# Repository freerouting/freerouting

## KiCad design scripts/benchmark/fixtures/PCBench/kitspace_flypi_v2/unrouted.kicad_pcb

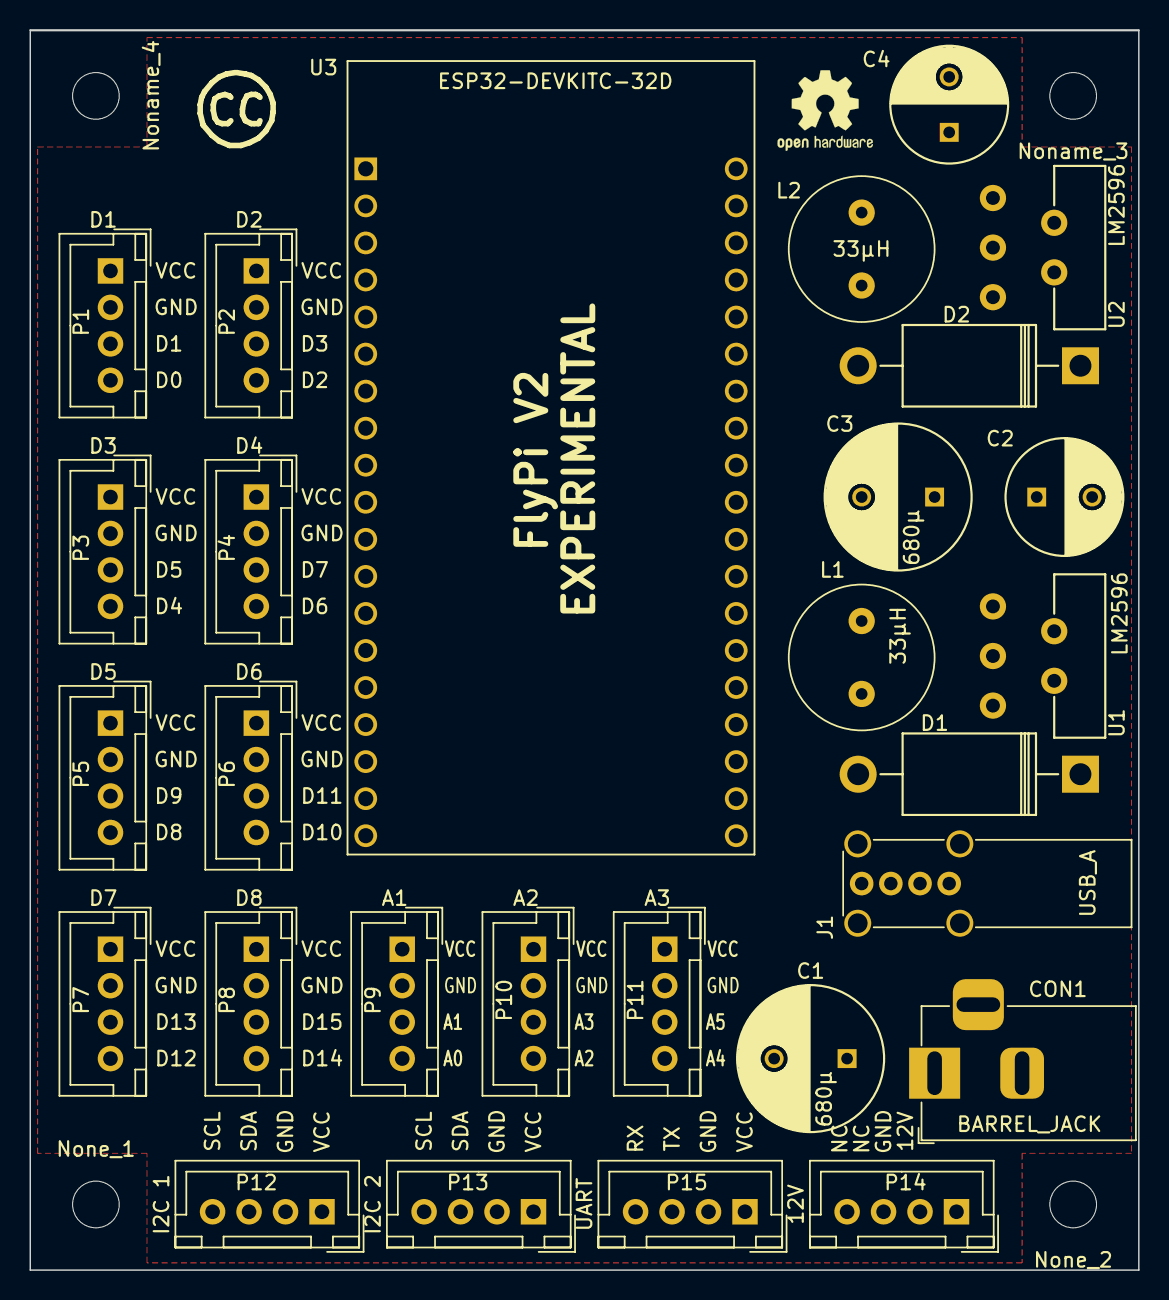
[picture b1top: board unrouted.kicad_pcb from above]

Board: 2 copper layers, 76.0 x 85.0 mm, 35 parts (0 on the bottom side), 34 nets, no tracks yet.

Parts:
C1, C3: 680µ; C_Radial_D10_L21_P5
C2, C4: 220µ; C_Radial_D8_L13_P3.8
CON1: BARREL_JACK; BarrelJack_Horizontal
D1, D2: Schottky 5A; Diode_DO-201AD_Horizontal_RM15
J1: USB_A; USB_A_Vertical
L1, L2: 33µH; Neosid_Inductor_MA-Bs75
Noname_1: Symbol_CreativeCommons_SilkScreenTop_Type2_Small
Noname_2: OSHW-Logo2_7.3x6mm_SilkScreen
Noname_3, Noname_4: MountingHole_3.2mm_M3_DIN965
Noname_5: (no value)
None_1, None_2: MountingHole_3.2mm_M3_DIN965
P1: D1; JST_XH_B04B-XH-A_04x2.50mm_Straight
P2: D2; JST_XH_B04B-XH-A_04x2.50mm_Straight
P3: D3; JST_XH_B04B-XH-A_04x2.50mm_Straight
P4: D4; JST_XH_B04B-XH-A_04x2.50mm_Straight
P5: D5; JST_XH_B04B-XH-A_04x2.50mm_Straight
P6: D6; JST_XH_B04B-XH-A_04x2.50mm_Straight
P7: D7; JST_XH_B04B-XH-A_04x2.50mm_Straight
P8: D8; JST_XH_B04B-XH-A_04x2.50mm_Straight
P9: A1; JST_XH_B04B-XH-A_04x2.50mm_Straight
P10: A2; JST_XH_B04B-XH-A_04x2.50mm_Straight
P11: A3; JST_XH_B04B-XH-A_04x2.50mm_Straight
P12: I2C 1; JST_XH_B04B-XH-A_04x2.50mm_Straight
P13: I2C 2; JST_XH_B04B-XH-A_04x2.50mm_Straight
P14: 12V; JST_XH_B04B-XH-A_04x2.50mm_Straight
P15: UART; JST_XH_B04B-XH-A_04x2.50mm_Straight
U1, U2: LM2596
U3: ESP32-DEVKITC-32D; MODULE_ESP32-DEVKITC-32D

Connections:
+5V: C4.1, L2.2, P1.1, P2.1, P3.1, P4.1, P5.1, P6.1, P7.1, P8.1, P9.1, P10.1, P11.1, P12.1, P13.1, P15.1, U2.4, U3.19
A1-3: P9.3, U3.6
A1-4: P9.4, U3.5
A2-3: P10.3, U3.4
A2-4: P10.4, U3.3
A3-3: P11.3, U3.33
A3-4: P11.4, U3.32
D1-3: P1.3, U3.8
D1-4: P1.4, U3.7
D2-3: P2.3, U3.10
D2-4: P2.4, U3.9
D3-3: P3.3, U3.12
D3-4: P3.4, U3.11
D4-3: P4.3, U3.15
D4-4: P4.4, U3.13
D5-3: P5.3, U3.17
D5-4: P5.4, U3.16
D6-3: P6.3, U3.18
D6-4: P6.4, U3.27
D7-3: P7.3, U3.36
D7-4: P7.4, U3.37
D8-3: P8.3, U3.35
D8-4: P8.4, U3.34
GND: C1.2, C2.2, C3.2, C4.2, CON1.2, CON1.3, D1.2, D2.2, J1.4, J1.5, P1.2, P2.2, P3.2, P4.2, P5.2, P6.2, P7.2, P8.2, P9.2, P10.2, P11.2, P12.2, P13.2, P14.2, P15.2, U1.3, U1.5, U2.3, U2.5, U3.14, U3.20, U3.26
I2C_1-3: P12.3, U3.29
I2C_1-4: P12.4, U3.28
I2C_2-3: P13.3, U3.31
I2C_2-4: P13.4, U3.30
unnamed: C1.1, C3.1, CON1.1, P14.1, U1.1, U2.1
unnamed: C2.1, J1.1, L1.2, U1.4
unnamed: D1.1, L1.1, U1.2
unnamed: D2.1, L2.1, U2.2
RX: P15.4, U3.24
TX: P15.3, U3.23

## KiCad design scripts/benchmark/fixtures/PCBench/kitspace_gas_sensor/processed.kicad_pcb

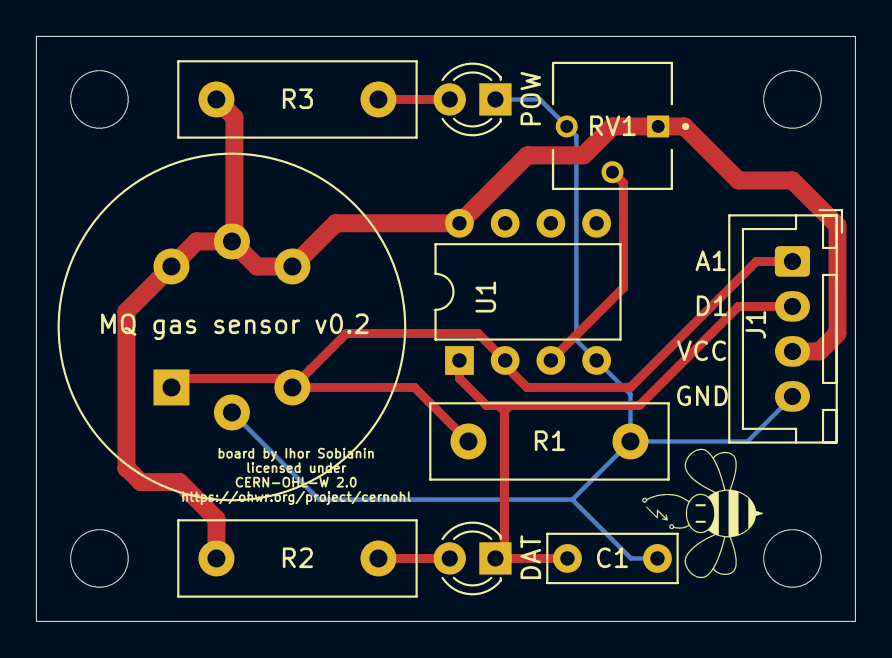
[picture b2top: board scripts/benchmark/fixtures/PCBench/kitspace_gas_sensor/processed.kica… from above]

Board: 2 copper layers, 45.5 x 32.5 mm, 10 parts (0 on the bottom side), 7 nets.

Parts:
A1: MQ-135; MQ-6
C1: 100nF; C_Disc_D7.0mm_W2.5mm_P5.00mm
D1, D2: LED; LED_D3.0mm
J1: Conn_01x04; JST_XH_B4B-XH-A_1x04_P2.50mm_Vertical
R1: 4,7k; R_Box_L13.0mm_W4.0mm_P9.00mm
R2, R3: 1k; R_Box_L13.0mm_W4.0mm_P9.00mm
RV1: R_POT; TRIM_3362P-1-103
U1: LM393; DIP-8_W7.62mm

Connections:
+5V: A1.4, A1.5, A1.6, J1.3, R2.1, R3.1, RV1.1, U1.8
A1: A1.1, A1.3, J1.1, R1.1, U1.2
D1: C1.1, D1.1, J1.2, U1.1
GND: A1.2, C1.2, D2.1, J1.4, R1.2, RV1.3, U1.4
unnamed: D1.2, R2.2
unnamed: D2.2, R3.2
unnamed: RV1.2, U1.3

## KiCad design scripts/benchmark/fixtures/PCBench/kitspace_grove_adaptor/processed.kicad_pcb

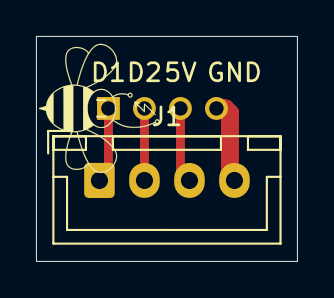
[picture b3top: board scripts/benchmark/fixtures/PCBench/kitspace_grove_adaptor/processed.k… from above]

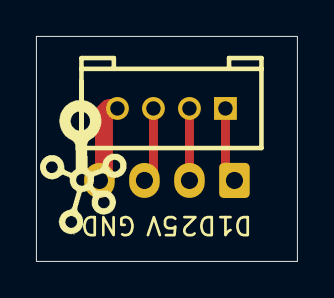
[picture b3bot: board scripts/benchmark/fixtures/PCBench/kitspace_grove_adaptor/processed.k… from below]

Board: 2 copper layers, 14.5 x 12.5 mm, 3 parts (2 on the bottom side), 4 nets.

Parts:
J1: Conn_01x04; JST_XH_B4B-XH-A_1x04_P2.50mm_Vertical
J2: Conn_01x04; 4P-LEADED-2.0
U$3: TWIGLOGO

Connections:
+5V: J1.3, J2.3
GND: J1.4, J2.4
unnamed: J1.1, J2.1
unnamed: J1.2, J2.2

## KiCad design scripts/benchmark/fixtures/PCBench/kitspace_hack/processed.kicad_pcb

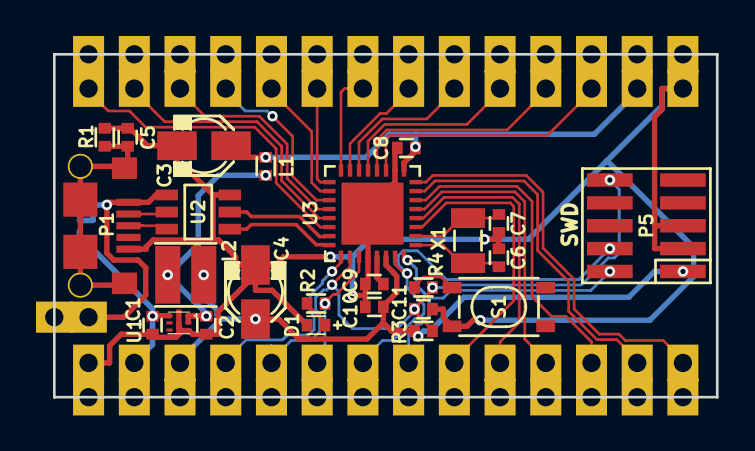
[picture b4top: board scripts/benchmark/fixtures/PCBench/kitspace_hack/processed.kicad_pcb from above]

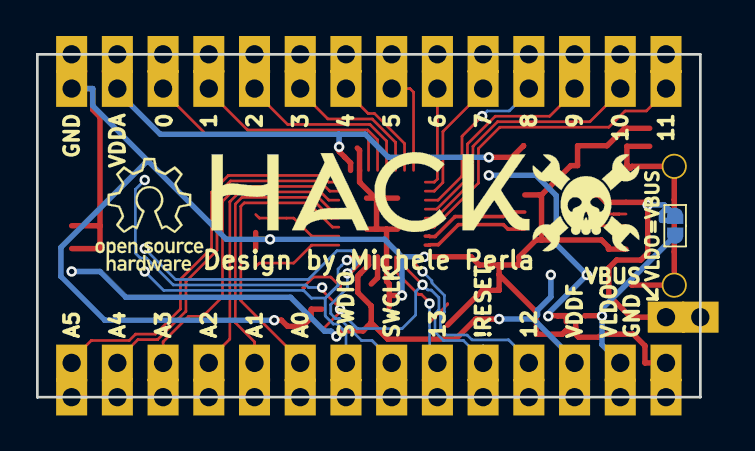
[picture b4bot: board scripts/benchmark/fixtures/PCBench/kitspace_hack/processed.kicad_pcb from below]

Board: 2 copper layers, 36.8 x 19.1 mm, 32 parts (6 on the bottom side), 39 nets.

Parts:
C1, C2: 2.2uF; C_0603
C3, C4: 10uF; c_elec_3x5.3
C5: 4.7nF; C_0603
C6, C7: 10pF; C_0603
C8, C9, C10, C11: 100nF; C_0603
D1: RED; LED_0603
JP1: Jumper_NO_Small; SMD_Jumper
L1: BLM18EG221; L_0603
L2: 10uH; ELLVFG
LOGO1: OSHW; OSHW-LOGO
LOGO2: HACKADAY; HACKADAY-LOGO
LOGO3: HACK; HACK-small
P1: USB_micro; 10118193-0001LF
P2, P3: CONN_01X14; Pin_Castellated_1x14
P4: CONN_01X01; Pin_Castellated_1x01
P5: CONN_SWD; Cortex_Debug_Connector_50mils
R1: 1M; R_0603
R2, R4: 330; R_0603
R3: 10k; R_0603
S1: RST; SPST-PTS_810
U1: MIC5528; DFN-6-1EP_1.2x1.2mm_Pitch0.4mm
U2: STF202; TSOP-6
U3: ATSAMD21E; QFN-32-1EP_5x5mm_Pitch0.5mm
X1: ABS07; xtal_3.2x1.5mm

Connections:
!RESET: C11.1, P2.5, P5.10, R3.1, R4.1, U3.26
/VDDCORE: C9.1, U3.29
/shield: C5.2, P1.6, R1.2
GND: C1.2, C2.2, C3.2, C4.2, C5.1, C6.2, C7.2, C8.2, C9.2, C10.2, C11.2, D1.2, P1.5, P2.1, P3.14, P5.3, P5.5, R1.1, S1.1, U1.3, U1.7, U2.6, U3.10, U3.28, U3.33
unnamed: D1.1, R2.2
unnamed: P1.2, U2.2
unnamed: P1.3, U2.3
unnamed: R4.2, S1.3
PA02/A0: P2.9, U3.3
PA03/A1: P2.10, U3.4
PA04/A2: P2.11, U3.5
PA05/A3: P2.12, U3.6
PA06/A4: P2.13, U3.7
PA07/A5: P2.14, U3.8
PA08/0: P3.12, U3.11
PA09/1: P3.11, U3.12
PA10/2: P3.10, U3.13
PA11/3: P3.9, U3.14
PA14/4: P3.8, U3.15
PA15/5: P3.7, U3.16
PA16/6: P3.6, U3.17
PA17/7: P3.5, U3.18
PA18/8: P3.4, U3.19
PA19/9: P3.3, U3.20
PA22/10: P3.2, U3.21
PA23/11: P3.1, U3.22
PA27/12: P2.4, U3.25
PA28/13: P2.6, R2.1, U3.27
PA30/SWCLK: P2.7, P5.4, U3.31
PA31/SWDIO: P2.8, P5.2, U3.32
USB-D+: U2.4, U3.24
USB-D-: U2.5, U3.23
VBUS: JP1.1, P1.1, P4.1, U2.1
VDD: C2.1, L1.1, L2.1, U1.1, U1.2
VDDANA: C3.1, C8.1, L1.2, P3.13, U3.9
VDDF: C4.1, C10.1, L2.2, P2.3, P5.1, R3.2, U3.30
VLDO: C1.1, JP1.2, P2.2, U1.6
XIN32: C6.1, U3.1, X1.1
XOUT32: C7.1, U3.2, X1.2

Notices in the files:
scripts/benchmark/fixtures/PCBench/kitspace_gas_sensor/processed.kicad_pcb:
licensed under
CERN-OHL-W 2.0
